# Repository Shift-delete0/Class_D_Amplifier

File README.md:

# Class_D_Amplifier
This is my project in which i have made a class D amplifier from scratch. I did this to challenge myself and learn more about analog electronics and amplifier. I have also designed an industrial level schematic and PCB using KiCad for the components which I had.

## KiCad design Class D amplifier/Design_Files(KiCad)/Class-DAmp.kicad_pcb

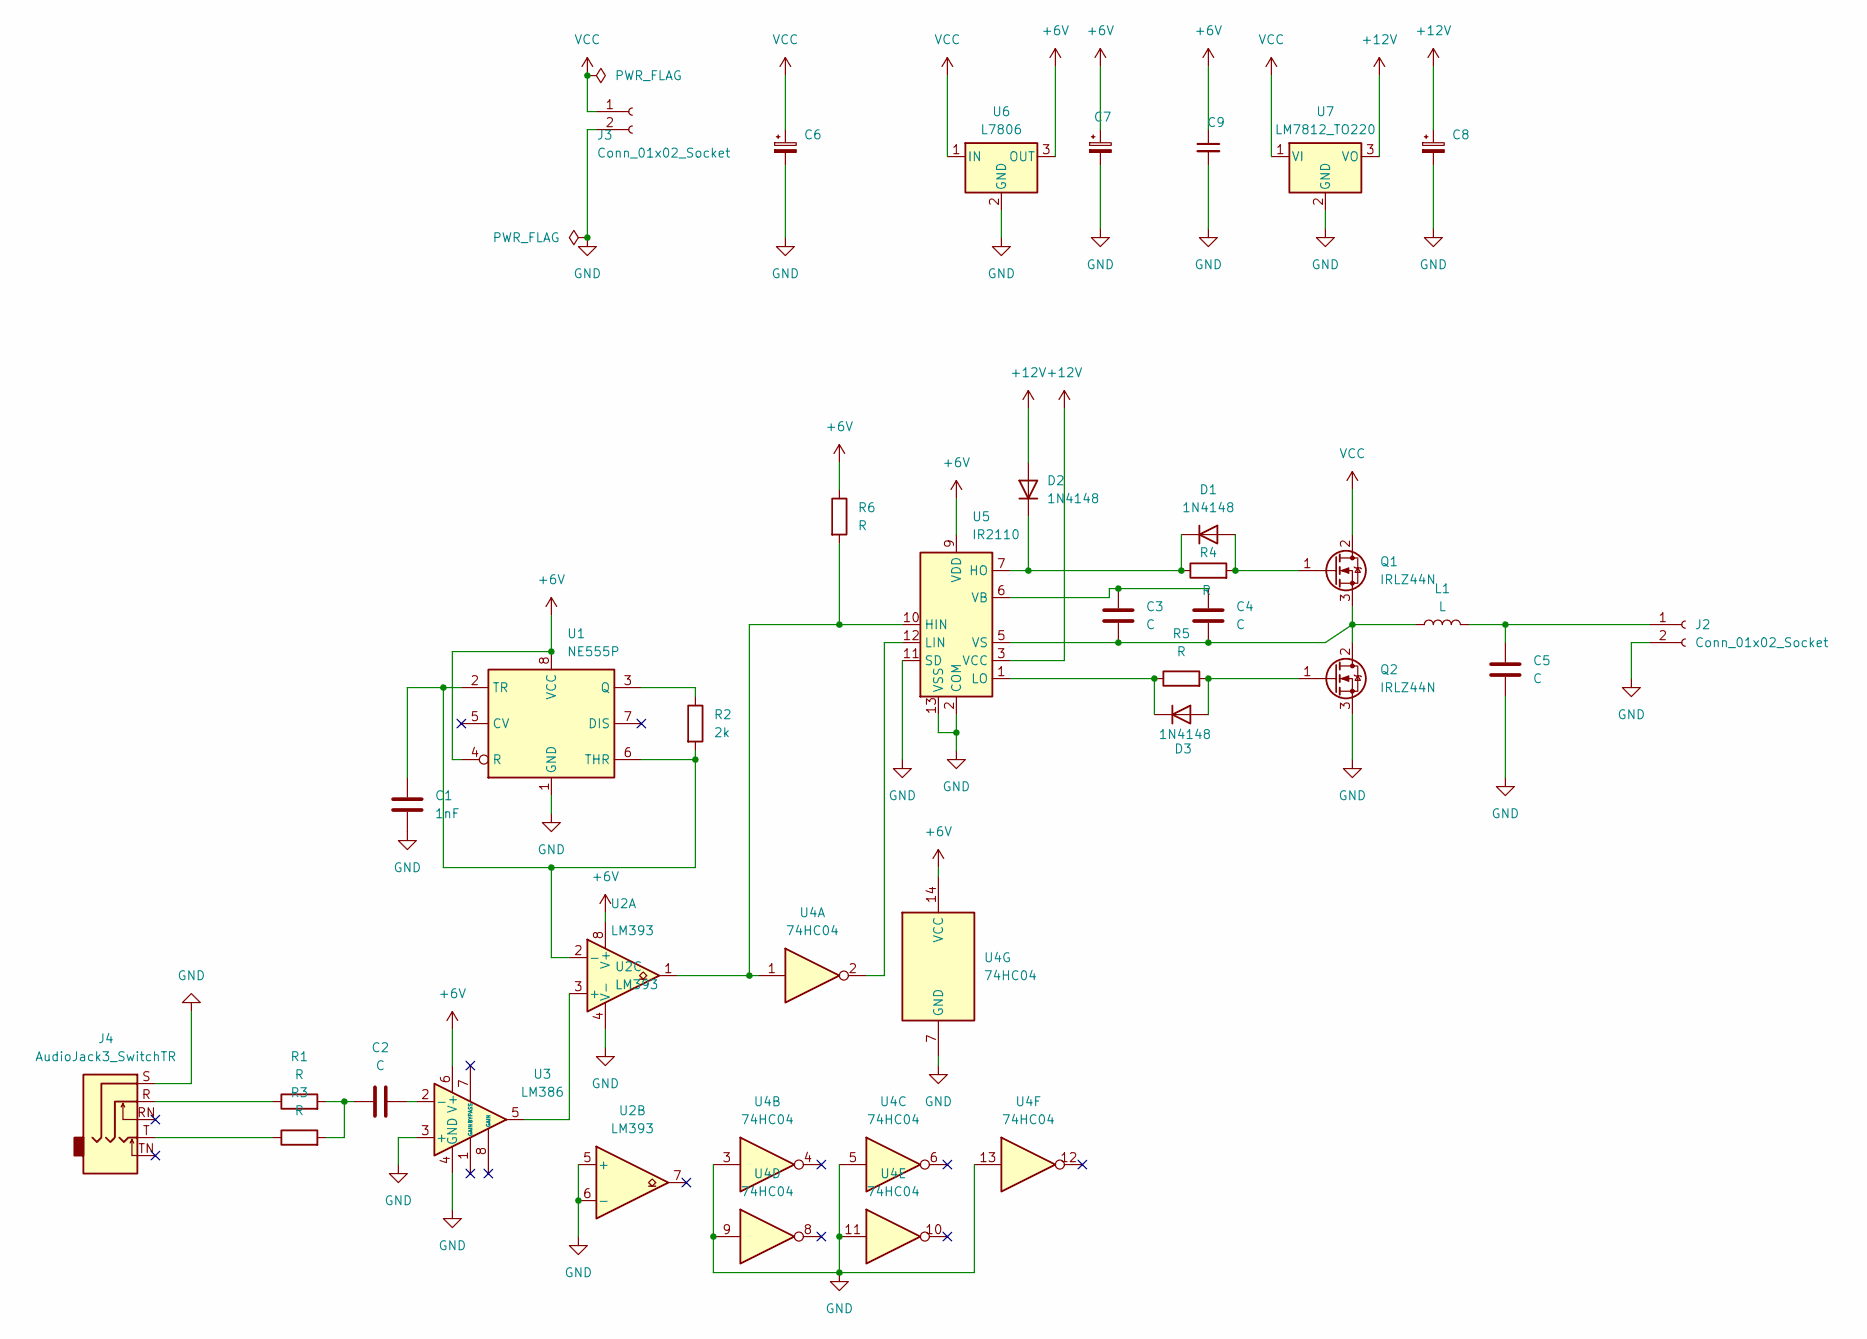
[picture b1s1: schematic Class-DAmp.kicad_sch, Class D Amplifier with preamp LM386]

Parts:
C1: 1nF; C_Disc_D3.8mm_W2.6mm_P2.50mm
C2: C; C_Rect_L10.3mm_W4.5mm_P7.50mm_MKS4
C3, C4: C; C_Disc_D3.8mm_W2.6mm_P2.50mm
C5: C; CP_Radial_D6.3mm_P2.50mm
C6, C7, C8: C_Polarized_Small; CP_Radial_D6.3mm_P2.50mm
C9: C_Small; C_Disc_D3.8mm_W2.6mm_P2.50mm
D1, D2, D3: 1N4148; D_DO-35_SOD27_P7.62mm_Horizontal
J2, J3: Conn_01x02_Socket; TerminalBlock_MaiXu_MX126-5.0-02P_1x02_P5.00mm
J4: AudioJack3_SwitchTR; Jack_3.5mm_CUI_SJ1-3525N_Horizontal
L1: L; L_Axial_L5.0mm_D3.6mm_P10.00mm_Horizontal_Murata_BL01RN1A2A2
Q1, Q2: IRLZ44N; TO-220-3_Vertical
R1, R3, R4, R5, R6: R; R_Axial_DIN0204_L3.6mm_D1.6mm_P1.90mm_Vertical
R2: 2k; R_Axial_DIN0204_L3.6mm_D1.6mm_P1.90mm_Vertical
U1: NE555P; DIP-8_W7.62mm
U2: LM393; DIP-8_W7.62mm
U3: LM386; DIP-8_W7.62mm
U4: 74HC04; DIP-14_W7.62mm
U5: IR2110; DIP-14_W7.62mm
U6: L7806; TO-220-3_Vertical
U7: LM7812_TO220; TO-220-3_Vertical

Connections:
+6V: C7.1, C9.1, R6.1, U1.4 (R), U1.8 (VCC), U2.8 (V+), U3.6 (V+), U4.14 (VCC), U5.9 (VDD), U6.3 (OUT)
+12V: C8.1, D2.2 (A), U5.3 (VCC), U7.3 (VO)
GND: C1.2, C5.2, C6.2, C7.2, C8.2, C9.2, J2.2, J3.2, J4.S, Q2.3 (S), U1.1 (GND), U2.4 (V-), U2.5 (+), U2.6 (-), U3.3 (+), U3.4 (GND), U4.3, U4.5, U4.7 (GND), U4.9, U4.11, U4.13, U5.2 (COM), U5.11 (SD), U5.13 (VSS), U6.2 (GND), U7.2 (GND)
unnamed: C2.1, R1.2, R3.2
unnamed: D1.2 (A), Q1.1 (G), R4.2
unnamed: D1.1 (K), D2.1 (K), R4.1, U5.7 (HO)
unnamed: D3.2 (A), Q2.1 (G), R5.2
unnamed: D3.1 (K), R5.1, U5.1 (LO)
unnamed: C5.1, J2.1, L1.2
unnamed: J4.R, R1.1
unnamed: J4.T, R3.1
unnamed: C3.2, C4.2, L1.1, Q1.3 (S), Q2.2 (D), U5.5 (VS)
unnamed: R2.1, U1.3 (Q)
unnamed: C1.1, R2.2, U1.2 (TR), U1.6 (THR), U2.2 (-)
unnamed: U2.3 (+), U3.5
unnamed: C2.2, U3.2 (-)
unnamed: R6.2, U2.1, U4.1, U5.10 (HIN)
unnamed: U4.2, U5.12 (LIN)
unnamed: C3.1, C4.1, U5.6 (VB)
VCC: C6.1, J3.1, Q1.2 (D), U6.1 (IN), U7.1 (VI)

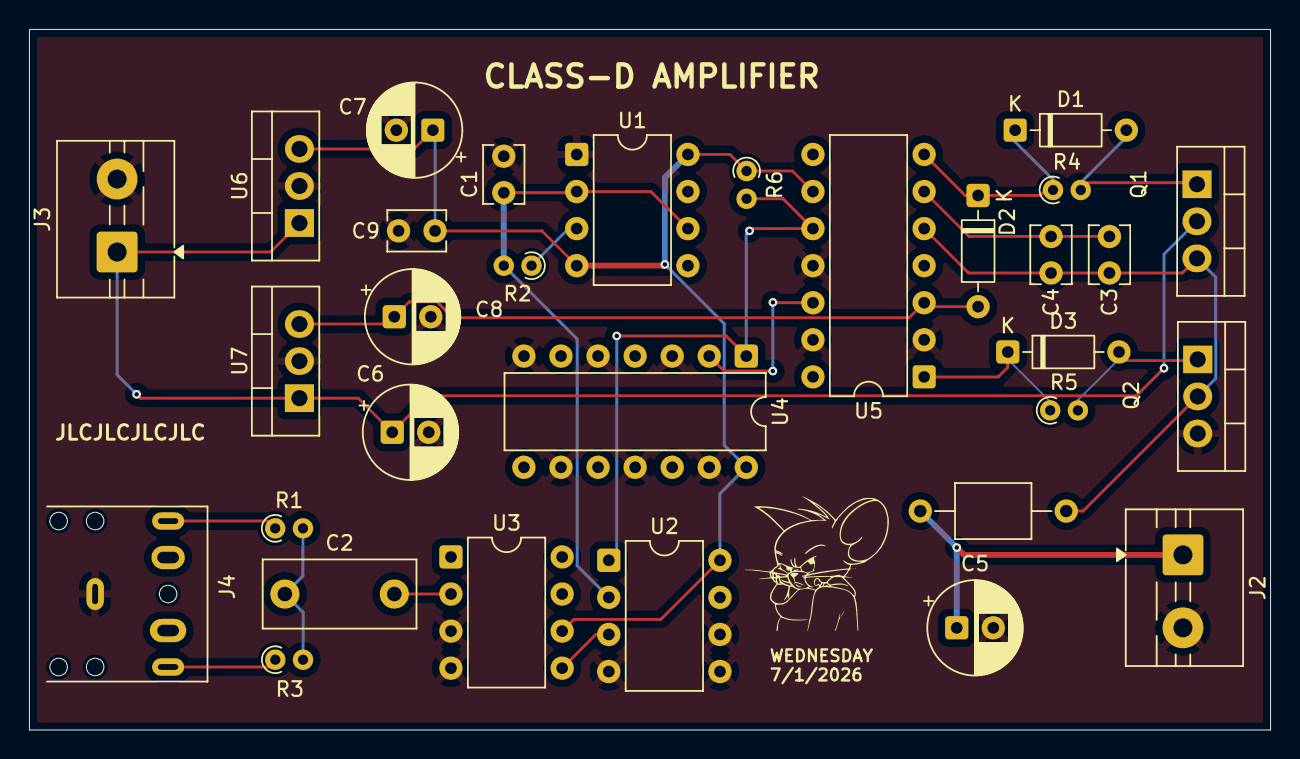
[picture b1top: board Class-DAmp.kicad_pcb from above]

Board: 4 copper layers, 85.0 x 48.0 mm, 31 parts (0 on the bottom side), 20 nets.

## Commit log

2026-03-17 README.md
